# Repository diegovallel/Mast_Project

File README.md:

# Mast_Project
Device development project

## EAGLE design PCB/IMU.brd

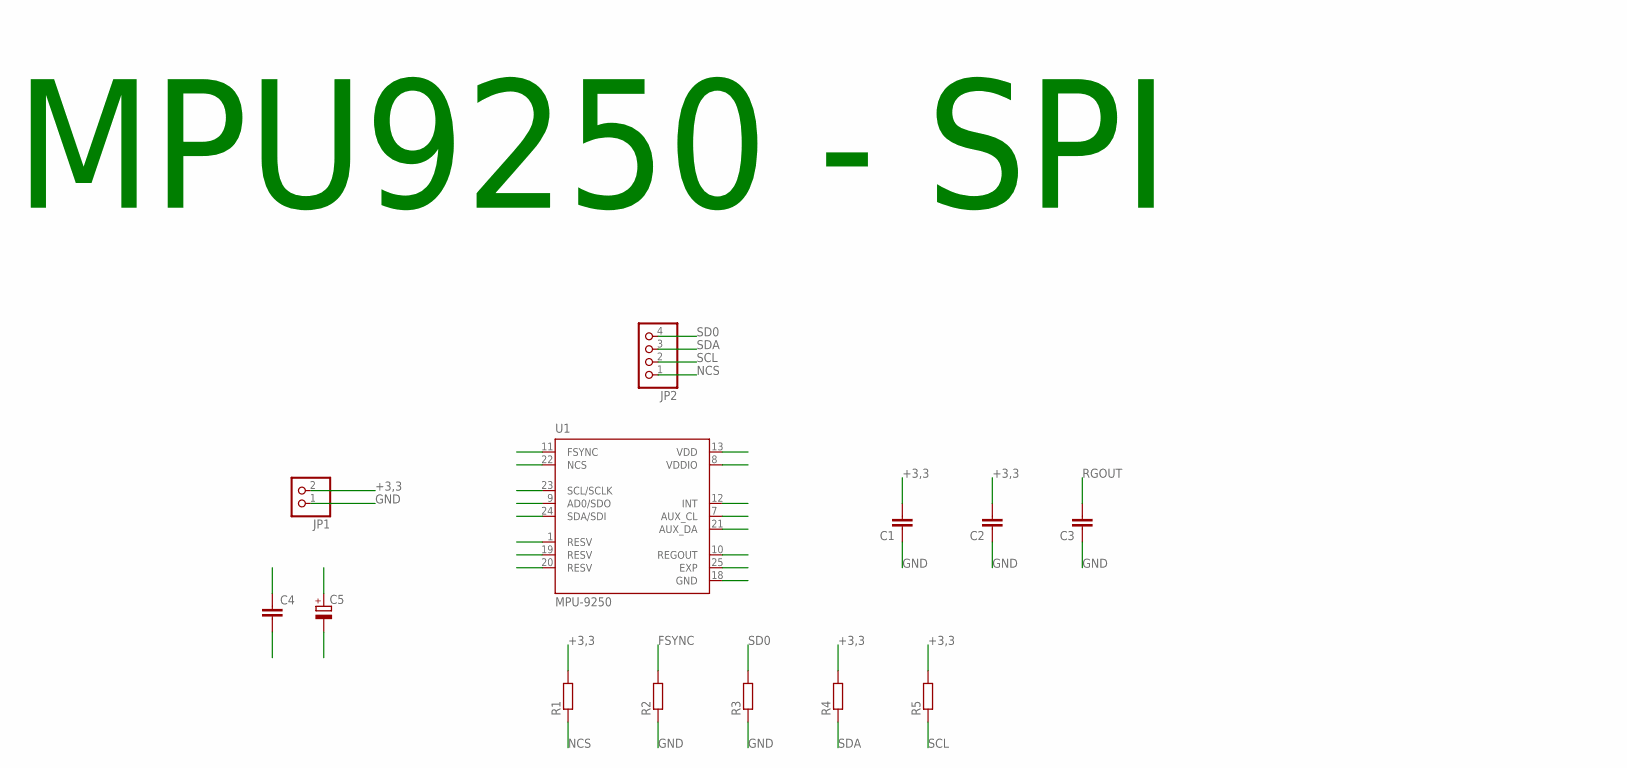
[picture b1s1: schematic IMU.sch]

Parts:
C1, C2, C3, C4: C-EUC0805; C0805
C5: CPOL-EUC/6032-28R; C/6032-28R
JP1: PINHD-1X2; 1X02
JP2: PINHD-1X4; 1X04
R1, R2, R3, R4, R5: R-EU_R0805; R0805
U1: MPU-9250; QFN40P300X300X105-25N

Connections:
+3,3: C1.2, C2.2, C4.1, C5.+, JP1.2, R1.2, R4.2, R5.2, U1.1 (RESV), U1.8 (VDDIO), U1.13 (VDD)
FSYNC: R2.2, U1.11 (FSYNC)
GND: C1.1, C2.1, C3.1, C4.2, C5.-, JP1.1, R2.1, R3.1, U1.18 (GND), U1.20 (RESV)
NCS: JP2.1, R1.1, U1.22 (NCS)
RGOUT: C3.2, U1.10 (REGOUT)
SCL: JP2.2, R5.1, U1.23 (SCL/SCLK)
SD0: JP2.4, R3.2, U1.9 (AD0/SDO)
SDA: JP2.3, R4.1, U1.24 (SDA/SDI)

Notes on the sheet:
MPU9250 - SPI

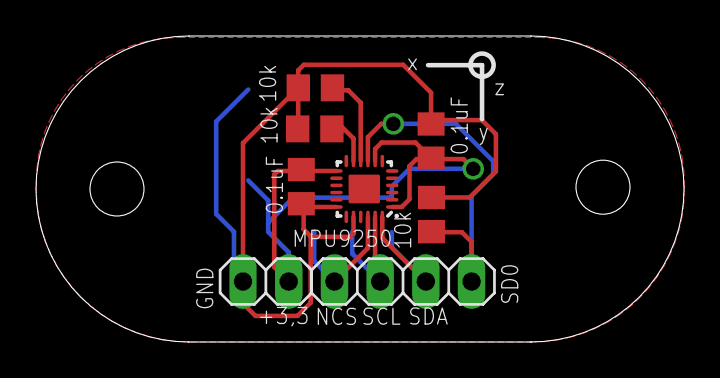
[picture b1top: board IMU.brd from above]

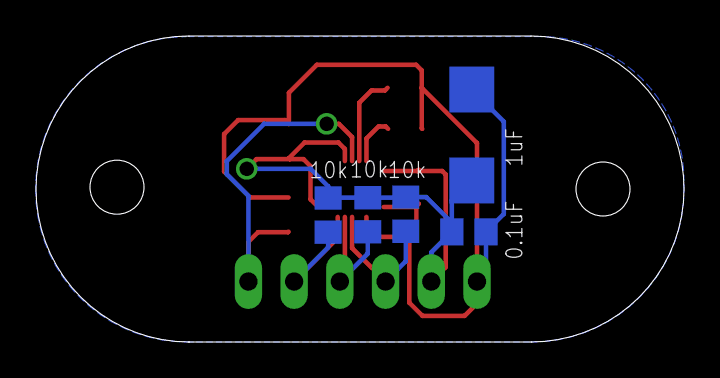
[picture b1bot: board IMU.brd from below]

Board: 2 copper layers, 36.0 x 17.0 mm, 13 parts (5 on the bottom side), 8 nets.

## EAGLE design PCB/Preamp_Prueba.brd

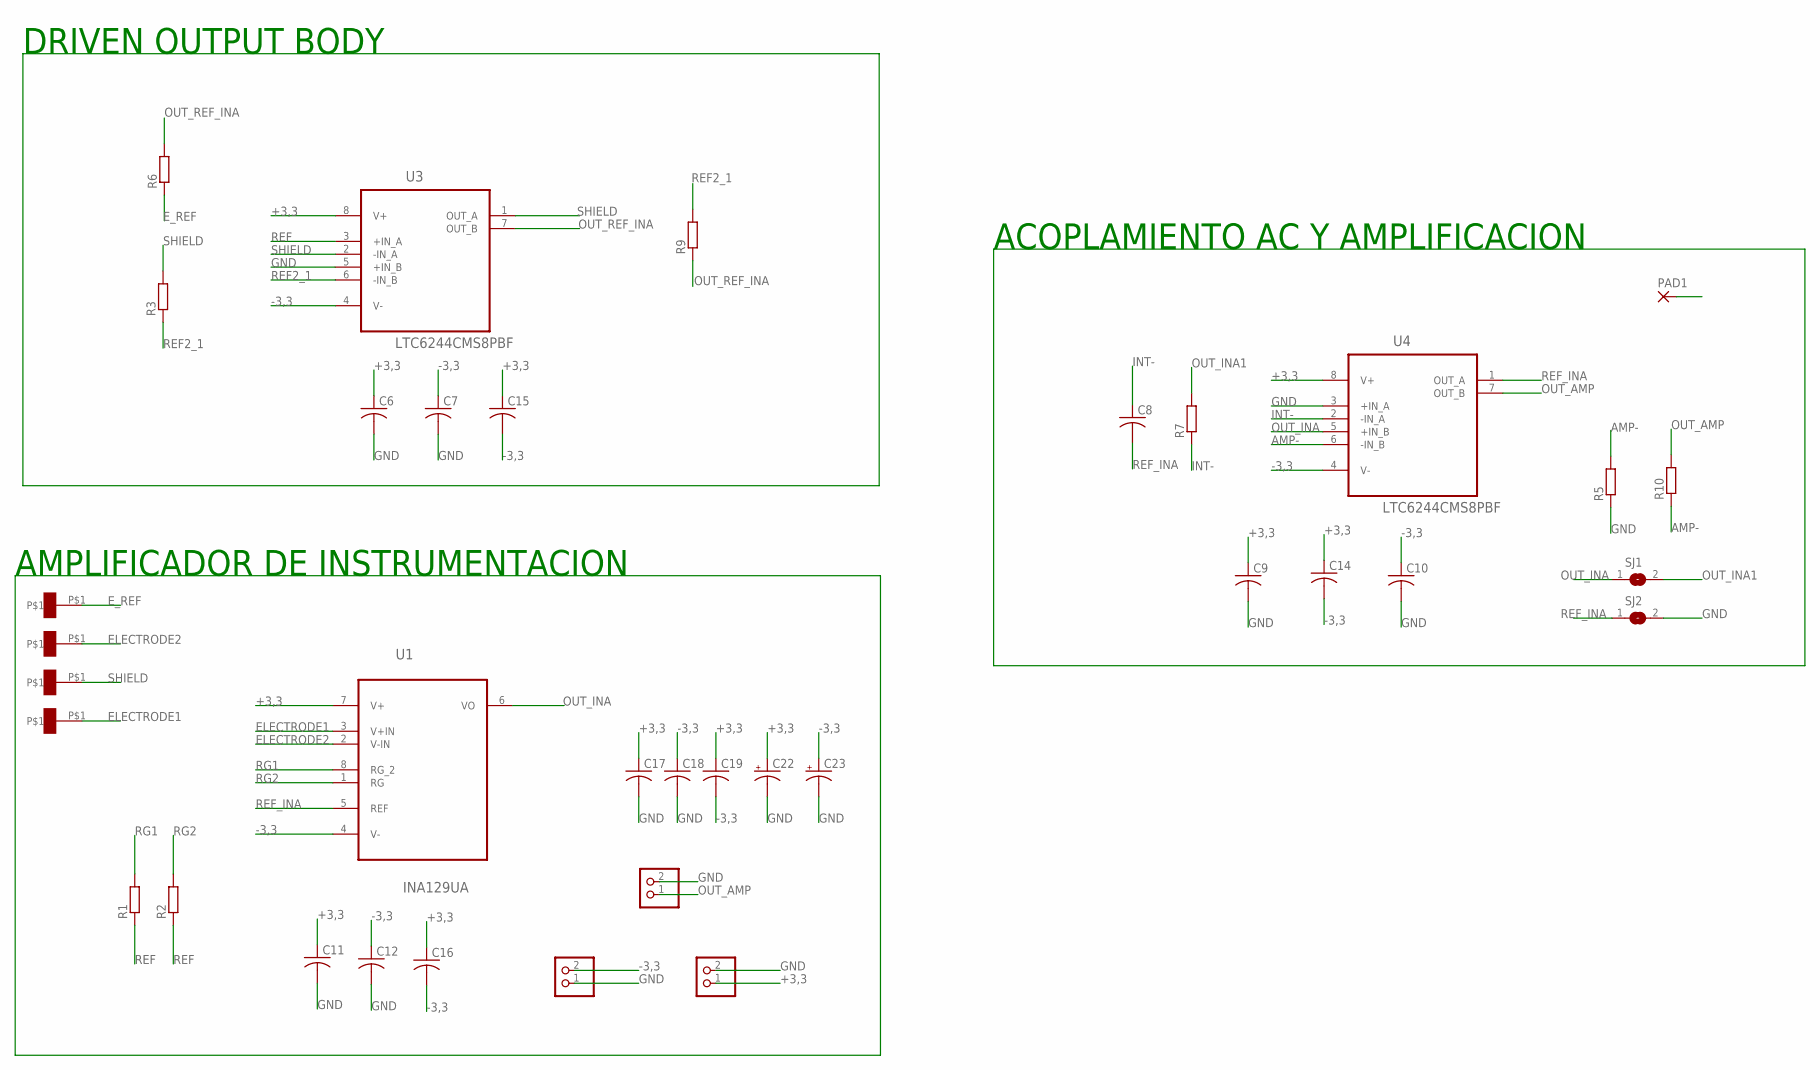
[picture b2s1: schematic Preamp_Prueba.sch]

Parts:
C6, C7, C8, C9, C10, C11, C12, C14, C15, C16, C17, C18, C19: C-USC0805; C0805
C22, C23: CPOL-USB/3528-21W; B/3528-21W
JP1, JP2, JP5: PINHD-1X2; 1X02
PAD1: SMD2; SMD1,27-2,54
R1, R2, R3, R5, R6, R7, R9, R10: R-EU_R0805; R0805
SJ1, SJ2: SJ
U1: INA129UA; SOIC127P600X175-8N
U3, U4: LTC6244CMS8PBF; SOP65P490X110-8N
U$1, U$2, U$3, U$4: PIN_E; PIN

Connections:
+3,3: C6.1, C9.1, C11.1, C14.1, C15.1, C16.1, C17.1, C19.1, C22.+, JP2.1, U1.7 (V+), U3.8 (V+), U4.8 (V+)
-3,3: C7.1, C10.1, C12.1, C14.2, C15.2, C16.2, C18.1, C19.2, C23.+, JP1.2, U1.4 (V-), U3.4 (V-), U4.4 (V-)
AMP-: R5.2, R10.1, U4.6 (-IN_B)
ELECTRODE1: U1.3 (V+IN), U$4.P$1
ELECTRODE2: U1.2 (V-IN), U$2.P$1
E_REF: R6.1, U$3.P$1
GND: C6.2, C7.2, C9.2, C10.2, C11.2, C12.2, C17.2, C18.2, C22.-, C23.-, JP1.1, JP2.2, JP5.2, PAD1.1, R5.1, SJ2.2, U3.5 (+IN_B), U4.3 (+IN_A)
INT-: C8.1, R7.1, U4.2 (-IN_A)
OUT_AMP: JP5.1, R10.2, U4.7 (OUT_B)
OUT_INA: SJ1.1, U1.6 (VO), U4.5 (+IN_B)
OUT_INA1: R7.2, SJ1.2
OUT_REF_INA: R6.2, R9.1, U3.7 (OUT_B)
REF: R1.1, R2.1, U3.3 (+IN_A)
REF2_1: R3.1, R9.2, U3.6 (-IN_B)
REF_INA: C8.2, SJ2.1, U1.5 (REF), U4.1 (OUT_A)
RG1: R1.2, U1.8 (RG_2)
RG2: R2.2, U1.1 (RG)
SHIELD: R3.2, U3.1 (OUT_A), U3.2 (-IN_A), U$1.P$1

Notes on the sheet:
AMPLIFICADOR DE INSTRUMENTACION
DRIVEN OUTPUT BODY
ACOPLAMIENTO AC Y AMPLIFICACION

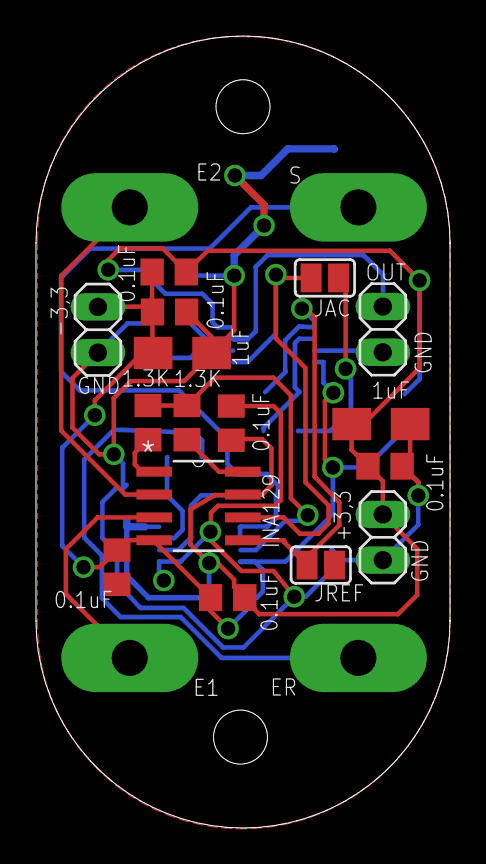
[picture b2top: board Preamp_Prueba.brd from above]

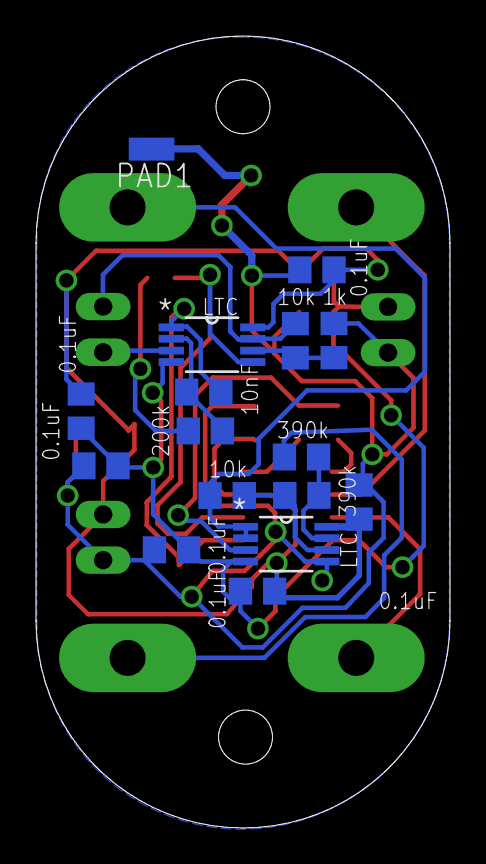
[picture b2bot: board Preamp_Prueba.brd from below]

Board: 2 copper layers, 23.0 x 44.0 mm, 36 parts (16 on the bottom side), 18 nets.

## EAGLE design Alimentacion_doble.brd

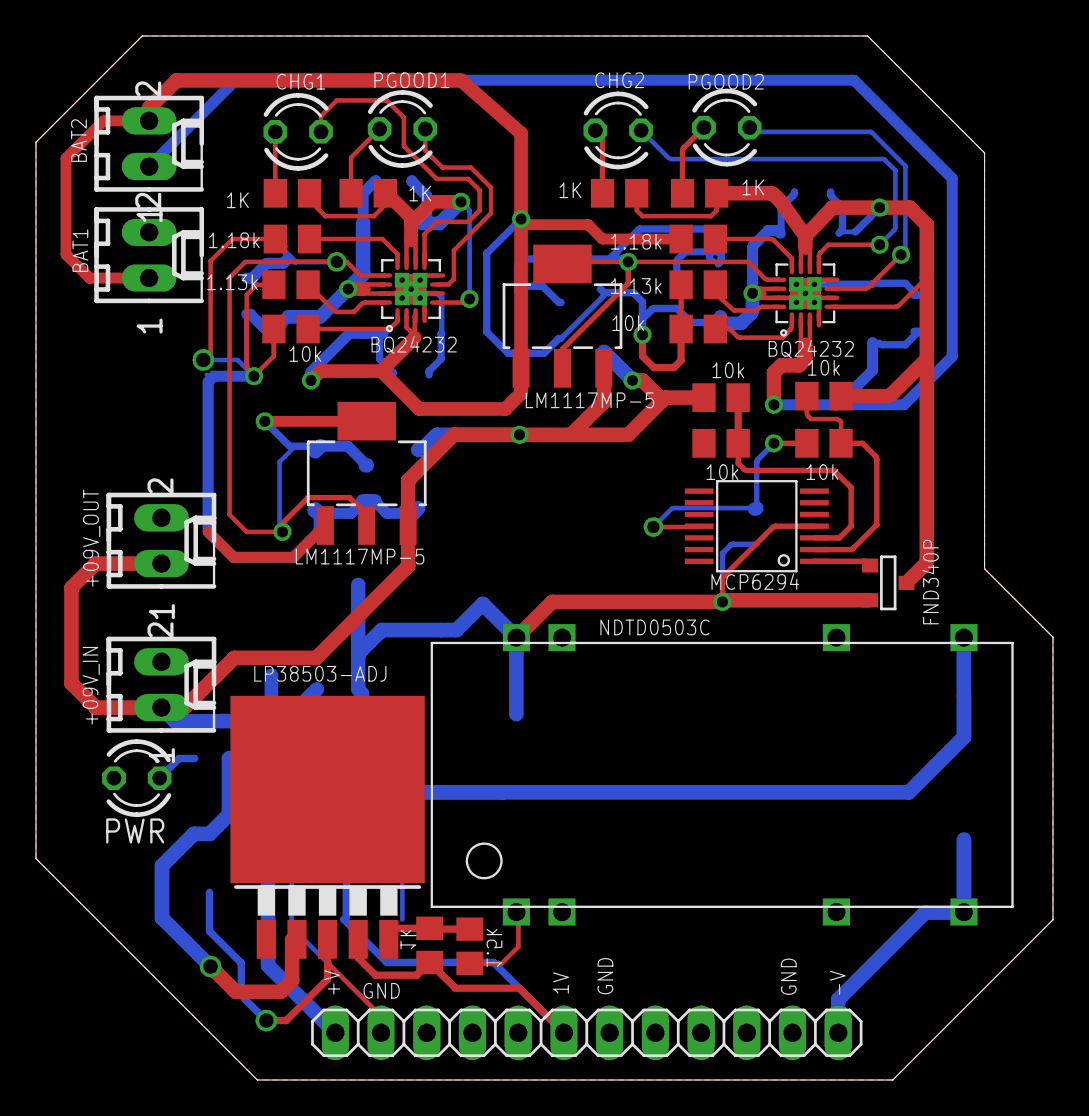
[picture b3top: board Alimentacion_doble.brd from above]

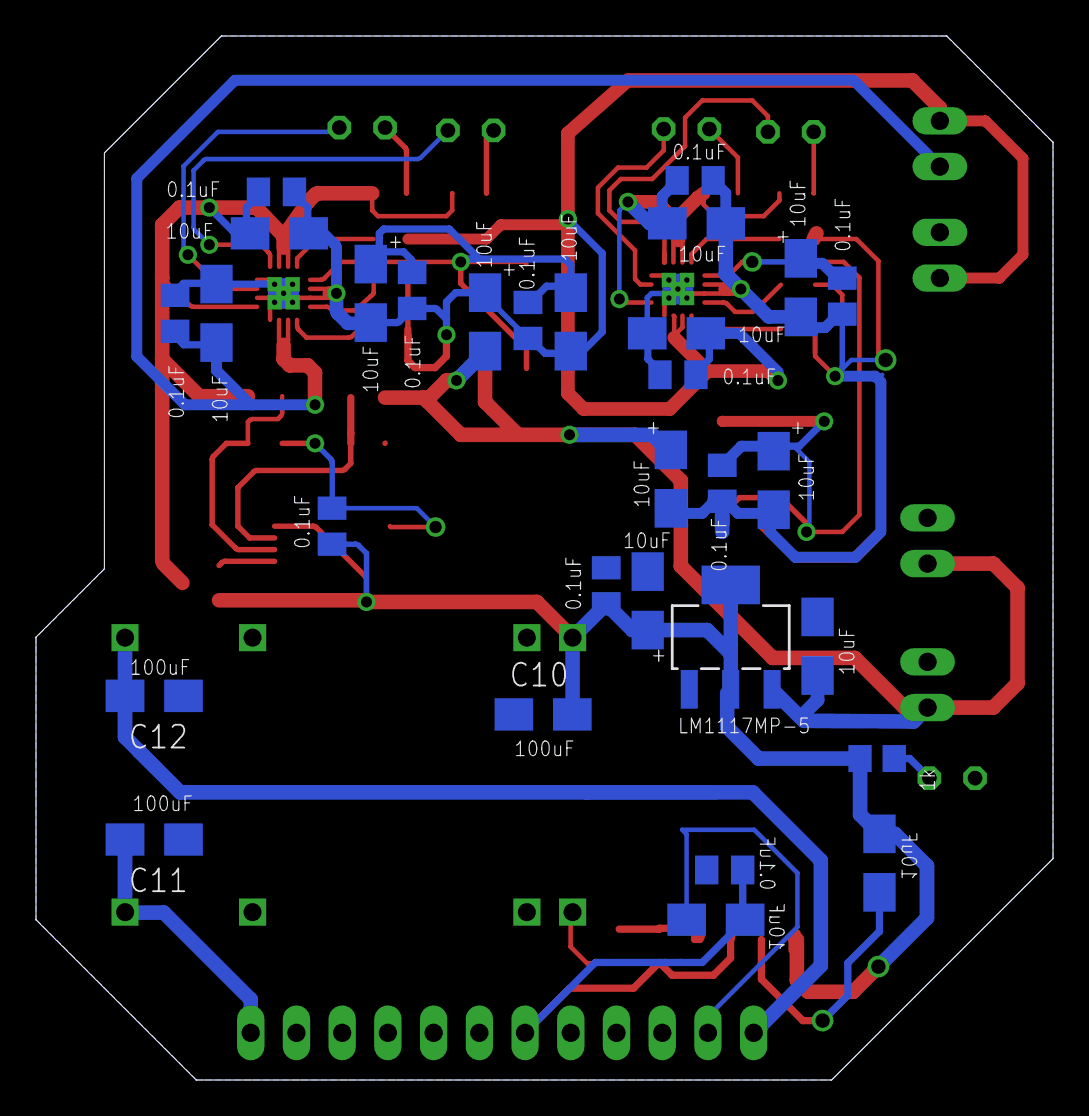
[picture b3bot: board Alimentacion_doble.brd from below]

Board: 2 copper layers, 56.5 x 58.0 mm, 64 parts (30 on the bottom side), 31 nets.

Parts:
C1, C3, C4, C7, C13, C18, C55, C63, C64, C65, C66: 0.1uF; C0805K
C2, C5, C6, C8, C9, C14, C15, C16, C17, C56, C57, C67, C68, C69: 10uF; B/3528-21W
C10, C11, C12: B/3528-21W
E$1: TO263-5
IC1, IC3, IC4: LM1117MP-5.0; SOT223
J1, J2: LED_BAT; 6410-02
J3: +12V_OUT; 6410-02
J4: +12V_IN; 6410-02
JP1: 1X12
LED1, LED2, LED6, LED12: LED3MM
PWR: PWR; LED3MM
R1, R2, R46, R47: 1K; M0805
R3, R48: 1.18k; M0805
R4, R49: 1.13k; M0805
R5, R34, R35, R36, R37, R50: 10k; M0805
R6, R7, R45: 1K; R0805
T1: T1; SOT-23
U$1, U$7: U7; BQ24232
U$2: NDTD_CONVERTER
U$10: U10; MCP6294

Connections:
1V: C13.1, C14.+, E$1.4, JP1.6, R6.1
5V_GND: C55.1, C56.+, C66.1, C69.+, IC3.2, IC3.4, U$7.13
5V_VREF: C4.1, C6.+, C7.1, C8.+, IC1.2, IC1.4, U$1.13
+3,3V: C12.+, JP1.1, U$2.5
+9V: C9.+, C16.+, C57.+, IC1.3, IC3.3, IC4.3, J3.1, J4.1, R36.1
-3,3V: C11.+, JP1.12, U$2.4
ADJ: E$1.5, R6.2, R7.1
BAT: C1.1, C2.+, J2.1, U$1.2, U$1.3
CHG: LED2.K, U$1.9
CHG1: LED12.K, U$7.9
COM_BAT: R34.2, R35.1, U$10.VINA-
COM_NET: R36.2, R37.1, U$10.VINA+
GATE_CMD: T1.3, U$10.VOUTA
GND: C10.-, C11.-, C12.-, C13.2, C14.-, C15.-, C16.-, C17.+, C18.1, C55.2, C56.-, C57.-, C63.2, C64.2, C65.2, C66.2, C67.-, C68.-, C69.-, E$1.3, E$1.6, IC3.1, IC4.1, J1.2, J3.2, J4.2, JP1.2, JP1.7, JP1.11, PWR.K, R7.2, R35.2, R37.2, R48.2, R49.2, R50.2, U$2.1, U$2.3, U$2.6, U$7.4, U$7.6, U$7.8, U$7.14, U$7.15, U$7.NA0, U$7.NA1, U$7.NA2, U$7.NA3, U$7.NA4, U$10.VSS
ILIM: R3.1, U$1.12
ILIM1: R48.1, U$7.12
ISET: R4.1, U$1.16
ISET1: R49.1, U$7.16
unnamed: LED1.A, R1.1
unnamed: LED2.A, R2.1
unnamed: PWR.A, R45.1
unnamed: LED6.A, R46.1
unnamed: LED12.A, R47.1
OUT_CH: C3.1, C5.+, R1.2, R2.2, R34.1, T1.1, U$1.5, U$1.10, U$1.11
OUT_CH1: C65.1, C68.+, R46.2, R47.2, U$7.5, U$7.10, U$7.11
PGOOD: LED1.K, U$1.7
PGOOD1: LED6.K, U$7.7
TS: R5.1, U$1.1
TS1: R50.1, U$7.1
VREF: C1.2, C2.-, C3.2, C4.2, C5.-, C6.-, C7.2, C8.-, C9.-, C64.1, C67.+, IC1.1, J1.1, J2.2, R3.2, R4.2, R5.2, U$1.4, U$1.6, U$1.8, U$1.14, U$1.15, U$1.NA0, U$1.NA1, U$1.NA2, U$1.NA3, U$1.NA4, U$7.2, U$7.3
V_IN: C10.+, C15.+, C17.-, C18.2, C63.1, E$1.2, IC4.2, IC4.4, R45.2, T1.2, U$2.8, U$10.VDD

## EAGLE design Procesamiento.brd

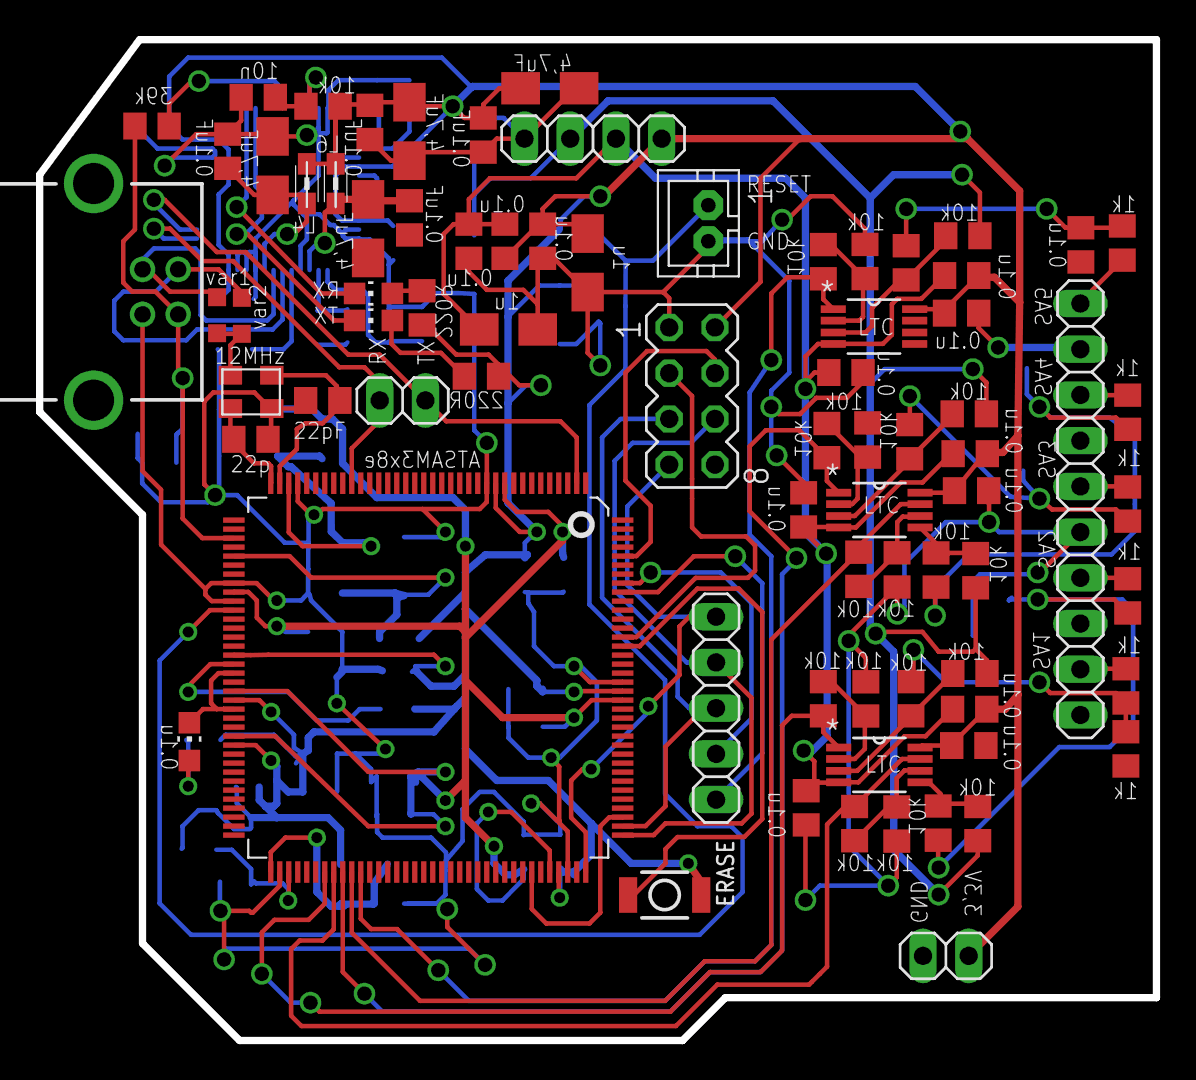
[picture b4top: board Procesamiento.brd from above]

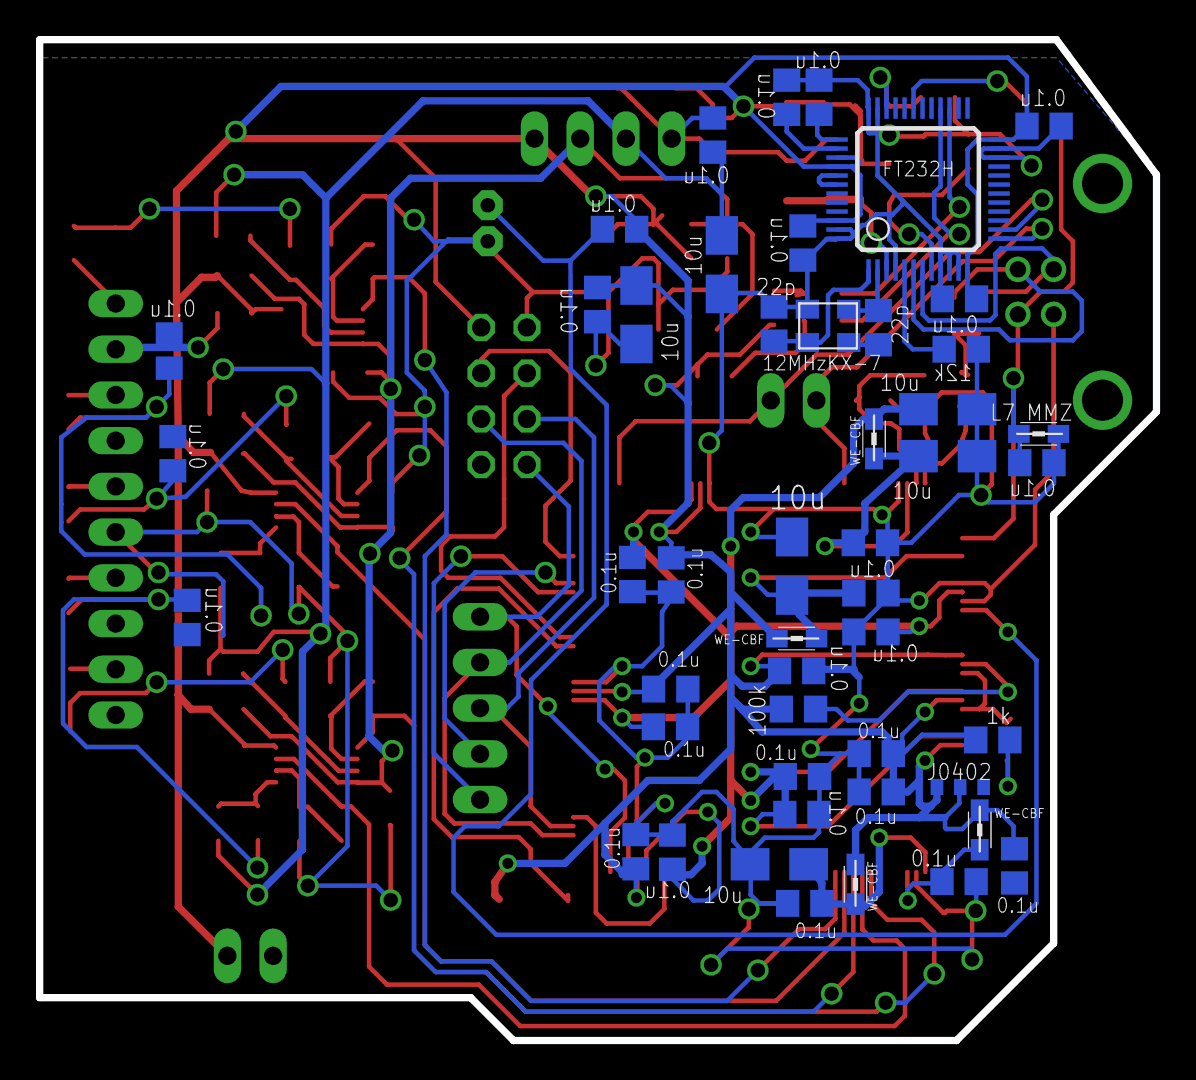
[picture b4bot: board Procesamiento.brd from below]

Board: 2 copper layers, 62.0 x 55.6 mm, 125 parts (48 on the bottom side), 66 nets.

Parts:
BR1: NM; J0402
C1, C2, C3, C4, C5, C6, C7, C8, C9, C10, C11, C12, C13, C14, C15, C16, C17, C18: C0805
CA1, CA31, CA33, CA37, CA39: 0,1u; C0805
CA2, CA7, CA11, CA13, CA14, CA27, CA28, CA29, CA30, CA32, CA34, CA38: 10u; B/3528-21W
CA3, CA4, CA5, CA6, CA8, CA9, CA10, CA12, CA15, CA16, CA17, CA18, CA19, CA20, CA22, CA23, CA26, CA40, CA41, CA42, CA43, CA44: 100n; C0805
CA21, CA35, CA45: 10n; C0805
CA24, CA47: 22p; C0805
CA25, CA46: 22pF; C0805
ERASE: SMD_157SW
IC1: FT232H; LQFP48
JP1: 1X05
JP2: 1X10
JP3: 1X04
JP4, JP8: 1X02
L1, L2, L3, L5: MH2029-300Y; 0805
L4, L6, L7: MMZ2012Y601B; 0805
ON, ON1, ON2: GREEN; CHIP-LED0805
P1: JST-PH2
R1, R2, R3, R4, R5, R6, R7, R8, R9, R10, R11, R12, R13, R14, R15, R16, R17, R18, R19, R20, R21, R22, R23, R24, R25, R26, R27, R28: R0805
RA1, RA2, RA3: 1k; R0805
RA5: 100k; R0805
SV1: MA04-2
U1, U2, U3: LTC6244CMS8PBF; SOP65P490X110-8N
UA1: ATSAM3X8EA-AU; LQFP144
X3: USBPTH; USB-B-PTH
Y1: 12MHz KX-7 20pF; CRYSTAL-3.2-2.5
Y2: 12MHzKX-7; CRYSTAL-3.2-2.5
Z1, Z2: CG0603MLC-05E; CT/CN0603

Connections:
+1: C13.1, CA29.+, JP3.2, R4.2, R8.2, R12.2, R16.2, R20.2
+3,3: BR1.2, BR1.3, C1.2, C3.2, C4.2, C6.2, C7.2, C9.2, C10.1, C12.1, CA1.1, CA2.+, CA3.1, CA4.1, CA5.1, CA6.1, CA7.+, CA8.1, CA9.1, CA21.1, CA22.1, CA30.+, CA31.1, CA38.+, CA39.1, CA42.1, CA43.1, CA44.1, ERASE.1, IC1.12, IC1.24, IC1.39, IC1.40, IC1.46, JP3.4, JP4.1, L1.1, L2.1, L3.1, L4.2, L6.2, R26.1, RA1.1, RA2.1, RA3.1, RA5.2, SV1.2, U1.8, U2.8, U3.8, UA1.11, UA1.52, UA1.57, UA1.62, UA1.105, UA1.125
-3,3: C2.2, C3.1, C5.2, C6.1, C8.2, C9.1, C11.1, C12.2, CA28.+, JP3.3, U1.4, U2.4, U3.4
A1+: R3.1, R4.1, U1.3
A1-: R1.2, R2.2, U1.2
A2+: R7.1, R8.1, U1.5
A2-: R5.2, R6.2, U1.6
A3+: R11.1, R12.1, U2.3
A3-: R9.2, R10.2, U2.2
A4+: R15.1, R16.1, U2.5
A4-: R13.2, R14.2, U2.6
A5+: R19.1, R20.1, U3.3
A5-: R17.2, R18.2, U3.2
AC7: IC1.31, R28.2
AO1: C14.1, R3.2, R21.1
AO2: C15.1, R7.2, R22.1
AO3: C16.1, R11.2, R23.1
AO4: C17.1, R15.2, R24.1
AO5: C18.1, R19.2, R25.1
AVREF: CA23.1, L3.2, UA1.75
CE: SV1.3, UA1.131
CSN: SV1.4, UA1.140
D+: IC1.7, X3.D+, Z1.1
D-: IC1.6, X3.D-, Z2.1
DL: R2.1, U1.1, UA1.79
DR: R6.1, U1.7, UA1.80
EL: R10.1, U2.1, UA1.81
EN3: UA1.102, UA1.111
ER: R14.1, U2.7, UA1.82
ERASE_S: ERASE.2, UA1.130
GND: C1.1, C2.1, C4.1, C5.1, C7.1, C8.1, C10.2, C11.2, C13.2, C14.2, C15.2, C16.2, C17.2, C18.2, CA1.2, CA2.-, CA3.2, CA4.2, CA5.2, CA6.2, CA7.-, CA8.2, CA9.2, CA10.2, CA11.-, CA12.2, CA13.-, CA14.-, CA15.2, CA16.2, CA17.2, CA18.2, CA19.2, CA20.2, CA22.2, CA23.2, CA24.2, CA25.2, CA26.2, CA27.-, CA28.-, CA29.-, CA30.-, CA31.2, CA32.-, CA33.2, CA34.-, CA35.2, CA37.2, CA38.-, CA39.2, CA40.2, CA41.2, CA42.2, CA43.2, CA44.2, CA45.2, CA46.2, CA47.2, IC1.4, IC1.9, IC1.10, IC1.11, IC1.22, IC1.23, IC1.35, IC1.36, IC1.41, IC1.42, IC1.47, IC1.48, JP2.1, JP2.3, JP2.5, JP2.7, JP2.9, JP3.1, JP4.2, L7.1, ON.C, P1.2, R1.1, R5.1, R9.1, R13.1, R17.1, R27.1, SV1.1, UA1.12, UA1.33, UA1.44, UA1.46, UA1.54, UA1.58, UA1.74, UA1.106, UA1.126, X3.GND, Y1.2, Y1.4, Y2.2, Y2.4, Z1.2, Z2.2
IR: R18.1, U3.1, UA1.83
MASTER-RESET: CA21.2, P1.1, UA1.47
MISO: JP1.5, SV1.7, UA1.108
MOSI: JP1.4, SV1.6, UA1.109
unnamed: ON.A, RA3.2
unnamed: ON1.A, RA1.2
unnamed: ON2.A, RA2.2
unnamed: RA5.1, UA1.53
NCS: JP1.2, UA1.137
NCS1: JP1.1, UA1.136
REF_H: IC1.5, R27.2
RESET: CA45.1, IC1.34, R26.2
RX: IC1.13, JP8.1, UA1.27
RXLED: IC1.27, ON1.C
SA1: JP2.2, R21.2
SA2: JP2.4, R22.2
SA3: JP2.6, R23.2
SA4: JP2.8, R24.2
SA5: JP2.10, R25.2
SPCK: JP1.3, SV1.5, UA1.110
TX: IC1.14, JP8.2, UA1.2
TXLED: IC1.28, ON2.C
VCCAH: CA41.1, IC1.37
VCCCORE: CA40.1, IC1.38
VDDANA: CA12.1, CA13.+, L1.2, UA1.73
VDDOUT: CA14.+, CA15.1, CA16.1, CA17.1, CA18.1, CA19.1, CA20.1, L5.1, UA1.10, UA1.45, UA1.56, UA1.61, UA1.104, UA1.124
VDDOUTMI: CA10.1, CA11.+, L2.2, UA1.41
VDDPLL: CA26.1, CA27.+, L5.2, UA1.34
VPHY: CA32.+, CA33.1, IC1.3, L6.1
VPLL: CA34.+, CA37.1, IC1.8, L4.1
XIN: CA24.1, UA1.36, Y1.1
XIN1: CA47.1, IC1.1, Y2.1
XOUT: CA25.1, UA1.35, Y1.3
XOUT1: CA46.1, IC1.2, Y2.3
XUSB: CA35.1, L7.2, R28.1, UA1.39, X3.VBUS
